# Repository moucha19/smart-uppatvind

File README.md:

Smart Uppatvind
===================

## Description

*Redesigned control board for IKEA Uppatvind with smart capabilities.*

The IKEA's air purifiyer lineup is very affordable, and that's especially true for the cheapest Uppatvind. Although it is not the most powerful, it can still improve air quality in a smaller room, while not taking a lot of space. Regardless of the pricepoint, there is not a lot of commercial options, that are this compact.

Unfortunately, it does not come with any smart controls, so I decided to create a replacement board, that should be reliable, relatively easy to make and that also provides some improvements over the original.

## Features

* Part for part replacement of the original - no modifications necessary
* Designed to be integrated into Home Assistent
* Flexible MCU options - both **ESP8684-WROOM-02C** and **ESP32-C3-WROOM-02C** are supported
* Adressable RGB for speed preset and filter life indicators
* Auto-reset circuit to simplify firmware flashing process
* **QWIIC** connector for external sensors
* Optional onboard EEPROM

*This project is not affiliated with or endorsed by IKEA. Use this design at your own risk. Ensure you follow proper safety protocols when handling electronic components and soldering.*

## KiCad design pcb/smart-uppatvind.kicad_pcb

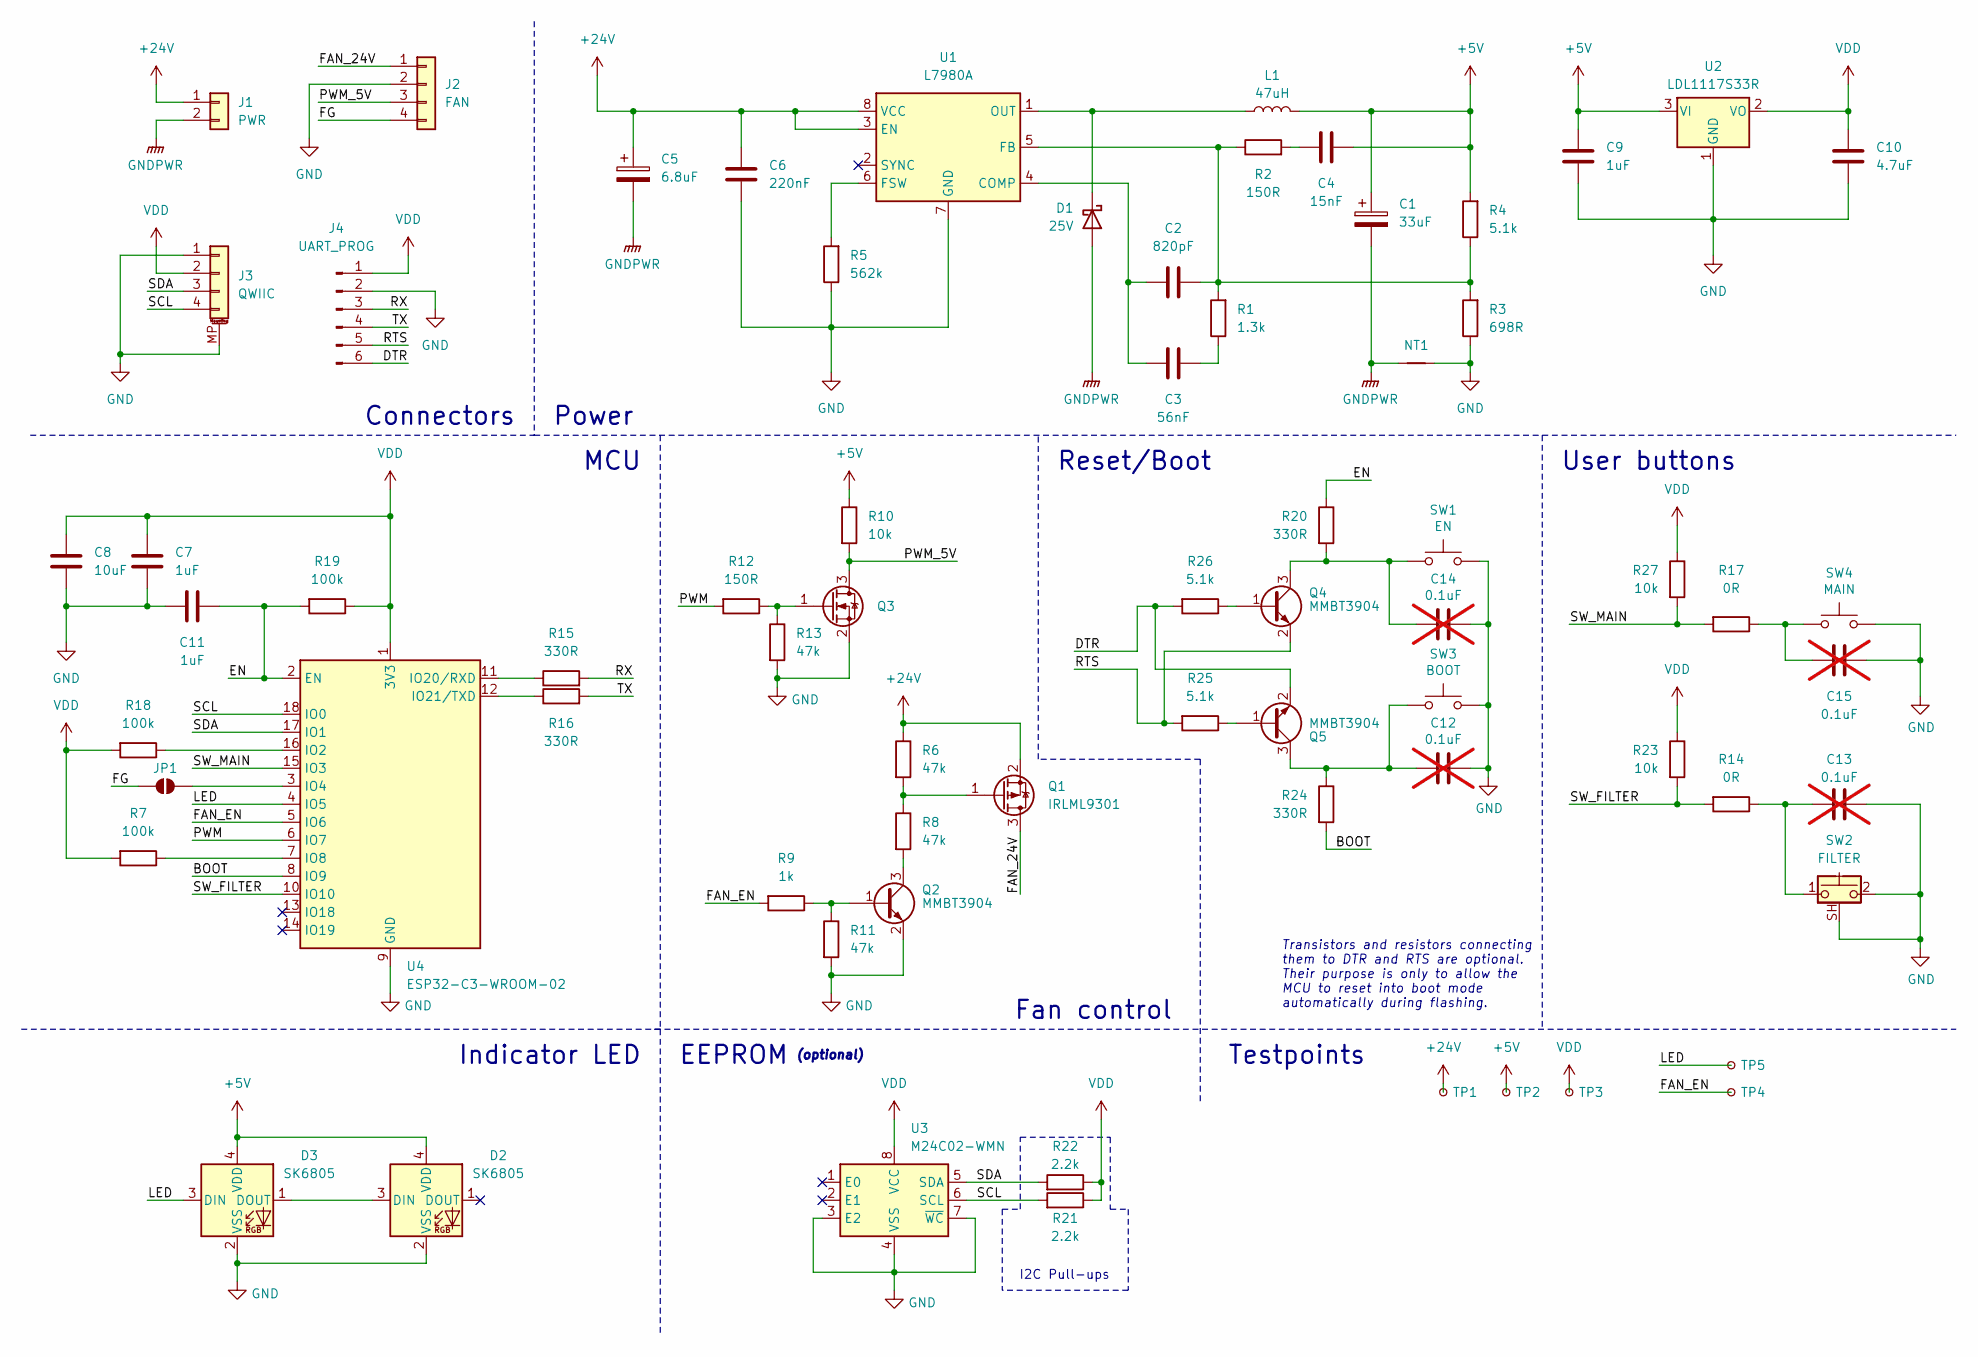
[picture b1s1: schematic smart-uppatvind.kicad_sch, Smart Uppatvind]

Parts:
C1: 33uF; CP_Elec_5x5.9
C2: 820pF; C_0805_2012Metric
C3: 56nF; C_0805_2012Metric
C4: 15nF; C_0805_2012Metric
C5: 6.8uF; C_Radial_D8.0mm_H7.0mm_P3.50mm
C6: 220nF; C_0805_2012Metric
C7, C9, C11: 1uF; C_0805_2012Metric
C8: 10uF; C_0805_2012Metric
C10: 4.7uF; C_0805_2012Metric
C12, C13, C14, C15: 0.1uF; C_0805_2012Metric; not fitted
D1: 25V; D_SMA
D2, D3: SK6805; LED_SK6805_EC14_1.4x1.4mm
J1: PWR; JST_XH_B2B-XH-A_1x02_P2.50mm_Vertical
J2: FAN; JST_XH_B4B-XH-A_1x04_P2.50mm_Vertical
J3: QWIIC; JST_SH_SM04B-SRSS-TB_1x04-1MP_P1.00mm_Horizontal
J4: UART_PROG; PinHeader_1x06_P2.54mm_Vertical
JP1: SolderJumper_2_Open; SolderJumper-2_P1.3mm_Open_RoundedPad1.0x1.5mm
L1: 47uH; L_Coilcraft_MSS1278H-XXX
NT1: NetTie-2_SMD_Pad2.0mm
Q1: IRLML9301; SOT-23
Q2, Q4, Q5: MMBT3904; SOT-23
Q3: Q_NMOS_GSD; SOT-23
R1: 1.3k; R_0805_2012Metric
R2, R12: 150R; R_0805_2012Metric
R3: 698R; R_0805_2012Metric
R4, R25, R26: 5.1k; R_0805_2012Metric
R5: 562k; R_0805_2012Metric
R6, R8, R11, R13: 47k; R_0805_2012Metric
R7, R18, R19: 100k; R_0805_2012Metric
R9: 1k; R_0805_2012Metric
R10, R23, R27: 10k; R_0805_2012Metric
R14, R17: 0R; R_0805_2012Metric
R15, R16: 330R; R_0805_2012Metric; LCSC C25104
R20, R24: 330R; R_0805_2012Metric
R21, R22: 2.2k; R_0805_2012Metric
SW1: EN; SW_Push_1P1T_Vertical_3x4mm; LCSC C589212
SW2: FILTER; SW_Tactile_G-Switch_GT-TC102B_Angled
SW3: BOOT; SW_Push_1P1T_Vertical_3x4mm; LCSC C589212
SW4: MAIN; SW_Push_K2-6639SP-C4_6x6mm_H5mm
TP1: VIN; TestPoint_THTPad_1.0x1.0mm_Drill0.5mm
TP2: +5V; TestPoint_THTPad_1.0x1.0mm_Drill0.5mm
TP3: VDD; TestPoint_THTPad_1.0x1.0mm_Drill0.5mm
TP4: FAN_EN; TestPoint_Pad_1.0x1.0mm
TP5: LED; TestPoint_Pad_1.0x1.0mm
U1: L7980A; HSOP-8-1EP_3.9x4.9mm_P1.27mm_EP2.3x2.3mm
U2: LDL1117S33R; SOT-223-3_TabPin2
U3: M24C02-WMN; SOIC-8_3.9x4.9mm_P1.27mm
U4: ESP32-C3-WROOM-02; ESP32-CX-WROOM-02

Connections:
+5V: C1.1, C4.2, C9.1, D2.4 (VDD), D3.4 (VDD), L1.2, R4.2, R10.1, TP2.1, U2.3 (VI)
+24V: C5.1, C6.1, J1.1, Q1.2 (S), R6.1, TP1.1, U1.3 (EN), U1.8 (VCC)
/BOOT: R24.2, U4.8 (IO9)
/DTR: J4.6, Q5.2 (E), R26.2
/EN: C11.1, R19.2, R20.1, U4.2 (EN)
/FAN_24V: J2.1, Q1.3 (D)
/FAN_EN: R9.2, TP4.1, U4.5 (IO6)
/FG: J2.4, JP1.1 (A)
/LED: D3.3 (DIN), TP5.1, U4.4 (IO5)
/PWM: R12.2, U4.6 (IO7)
/PWM_5V: J2.3, Q3.3 (D), R10.2
/RTS: J4.5, Q4.2 (E), R25.2
/RX: J4.3, R15.2
/SCL: J3.4, R21.2, U3.6 (SCL), U4.18 (IO0)
/SDA: J3.3, R22.2, U3.5 (SDA), U4.17 (IO1)
/SW_FILTER: R14.2, R23.2, U4.10 (IO10)
/SW_MAIN: R17.2, R27.2, U4.15 (IO3)
/TX: J4.4, R16.2
GND: C6.2, C7.2, C8.2, C9.2, C10.2, C11.2, C12.1, C13.1, C14.1, C15.1, D2.2 (VSS), D3.2 (VSS), J2.2, J3.1, J3.MP (MountPin), J4.2, NT1.2, Q2.2 (E), Q3.2 (S), R3.1, R5.1, R11.2, R13.2, SW1.2, SW2.2, SW2.SH (B), SW3.2, SW4.2, U1.7 (GND), U1.9 (GND), U2.1 (GND), U3.3 (E2), U3.4 (VSS), U3.7 (~WC), U4.9 (GND), U4.19 (GND)
GNDPWR: C1.2, C5.2, D1.2 (A), J1.2, NT1.1
unnamed: C3.2, R1.1
unnamed: C4.1, R2.2
unnamed: C13.2, R14.1, SW2.1
unnamed: C15.2, R17.1, SW4.1
unnamed: D1.1 (K), L1.1, U1.1 (OUT)
unnamed: D2.3 (DIN), D3.1 (DOUT)
unnamed: JP1.2 (B), U4.3 (IO4)
unnamed: Q1.1 (G), R6.2, R8.1
unnamed: Q2.1 (B), R9.1, R11.1
unnamed: Q2.3 (C), R8.2
unnamed: Q3.1 (G), R12.1, R13.1
unnamed: Q4.1 (B), R26.1
unnamed: C14.2, Q4.3 (C), R20.2, SW1.1
unnamed: Q5.1 (B), R25.1
unnamed: C12.2, Q5.3 (C), R24.1, SW3.1
unnamed: C2.1, C3.1, U1.4 (COMP)
unnamed: C2.2, R1.2, R2.1, R3.2, R4.1, U1.5 (FB)
unnamed: R5.2, U1.6 (FSW)
unnamed: R18.1, U4.16 (IO2)
unnamed: R7.1, U4.7 (IO8)
unnamed: R15.1, U4.11 (IO20/RXD)
unnamed: R16.1, U4.12 (IO21/TXD)
VDD: C7.1, C8.1, C10.1, J3.2, J4.1, R7.2, R18.2, R19.1, R21.1, R22.1, R23.1, R27.1, TP3.1, U2.2 (VO), U3.8 (VCC), U4.1 (3V3)

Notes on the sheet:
Connectors
(optional)
Reset/Boot
Testpoints
EEPROM
Power
MCU
Fan control
Transistors and resistors connecting them to DTR and RTS are optional. Their purpose is only to allow the MCU to reset into boot mode automatically during flashing.
I2C Pull-ups
Indicator LED
User buttons

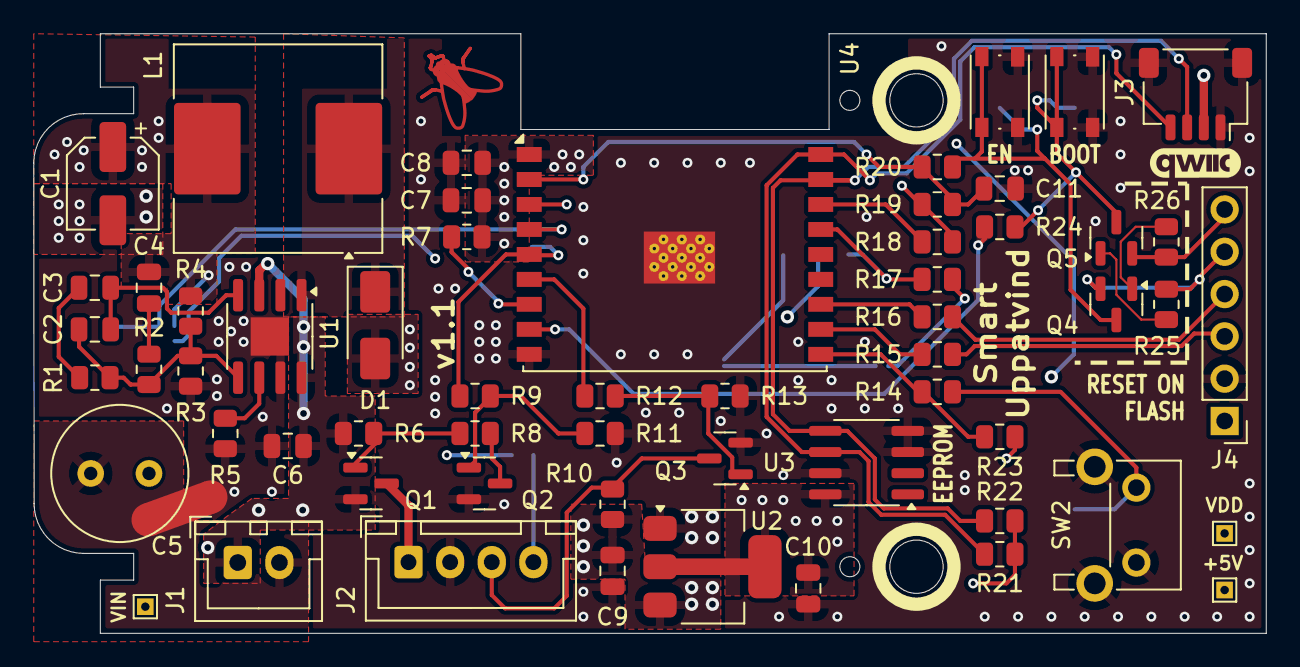
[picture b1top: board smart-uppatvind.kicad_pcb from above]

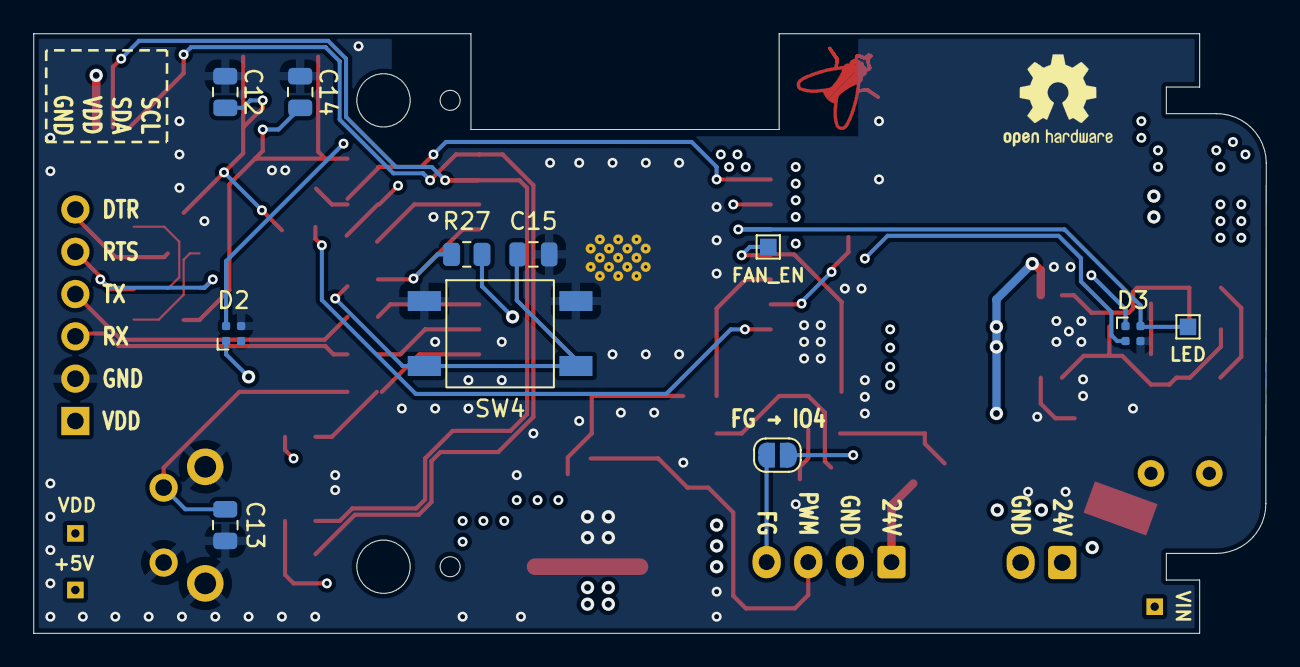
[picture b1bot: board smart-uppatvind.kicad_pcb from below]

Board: 4 copper layers, 74.0 x 36.0 mm, 70 parts (11 on the bottom side), 43 nets.

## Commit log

2024-07-15 Adjusted layout
2024-07-15 Partly routed power management
2024-07-16 Adjusted MCU pin assignment, progressed with power routing
2024-07-18 Added logos
2024-07-18 Routed all signals, added connector pinout labels
2024-07-18 Finishing touches, via stitching
2024-07-19 Minor adjustments, added missing 3D models
2024-07-19 Fixed inverted signals on main connectors, added generated schematic
2024-12-14 Formatted some resistor values
2024-12-14 Improved the schematic readability by grouping it into named segments
2024-12-15 Fixed incorrect connection of strapping pins for ESP32-C3
2024-12-15 Added back EEPROM text, cleaned up tracks
2024-12-15 Connected shield pins of filter switch, made switch pull-ups not optional
2024-12-15 Removed R_Small symbols for consistency
2024-12-15 Unified resistor footprints - removed handsolder variants
2024-12-15 Optimized routing
2024-12-29 Added feature list and short introduction
2024-12-29 Added testpoints
2024-12-30 Reannotated components geographically, adjusted designator positions
2025-01-19 Added test point labels to back side, added OSHW symbol
2025-01-26 Added board photo and render

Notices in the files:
pcb/smart-uppatvind.kicad_pcb:
Licensed under CERN-OHL-W v2
